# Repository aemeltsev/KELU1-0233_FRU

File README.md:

# KELU1-0233_FRU

![PCB image][KELU1-0233_FRU
]

[KELU1-0233_FRU]:https://github.com/aemeltsev/KELU1-0233_FRU/blob/master/hw/KELU1-0233_PCB.png

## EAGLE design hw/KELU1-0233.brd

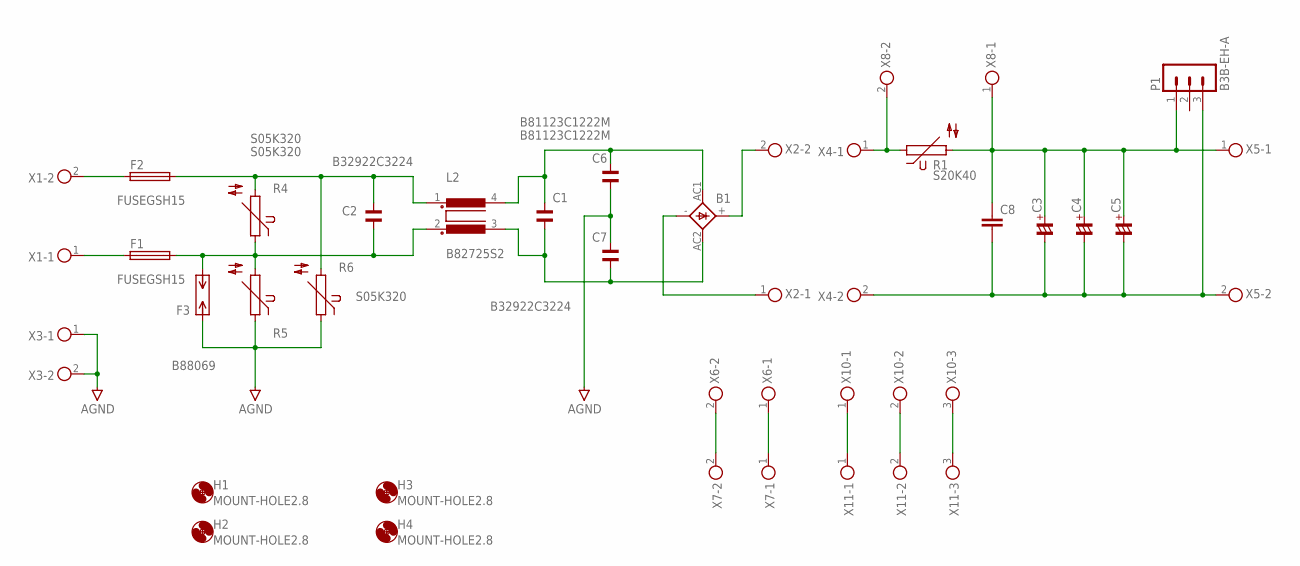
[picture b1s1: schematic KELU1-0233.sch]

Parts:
B1: FBM
C1, C2: B32922C3224; C150-054X183
C3, C4, C5: CPOL-EUE7.5-18; E7,5-18
C6, C7: B81123C1222M; C150-054X183
C8: C-EU102-043X133; C102-043X133
F1, F2: FUSEGSH15; GSH15
F3: B88069; N81
H1, H2, H3, H4: MOUNT-HOLE2.8; 2,8
L2: B82725S2; PLC
P1: B3B-EH-A
R1: S20K40
R4, R5, R6: S05K320; S05K300
X1, X2, X3, X4, X5, X6, X7, X8: DG129-7.5-02P; DG129-7.5-02P-14-00A
X10, X11: DG129-7.5-03P; DG129-7.5-03P-14-00A

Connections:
AGND: C6.2, C7.1, F3.P$1 (A), R5.1, R6.1, X3.1, X3.2
unnamed: C2.1, F2.2, L2.1, R4.2, R6.2
unnamed: C2.2, F1.2, F3.P$2 (B), L2.2, R4.1, R5.2
unnamed: F1.1, X1.1
unnamed: B1.AC1, C1.1, C6.1, L2.4
unnamed: B1.AC2, C1.2, C7.2, L2.3
unnamed: F2.1, X1.2
unnamed: B1.-, X2.1
unnamed: B1.+, X2.2
unnamed: C3.-, C4.-, C5.-, C8.2, P1.3, X4.2, X5.2
unnamed: C3.+, C4.+, C5.+, C8.1, P1.1, R1.2, X5.1, X8.1
unnamed: R1.1, X4.1, X8.2
unnamed: X6.2, X7.2
unnamed: X6.1, X7.1
unnamed: X10.1, X11.1
unnamed: X10.2, X11.2
unnamed: X10.3, X11.3

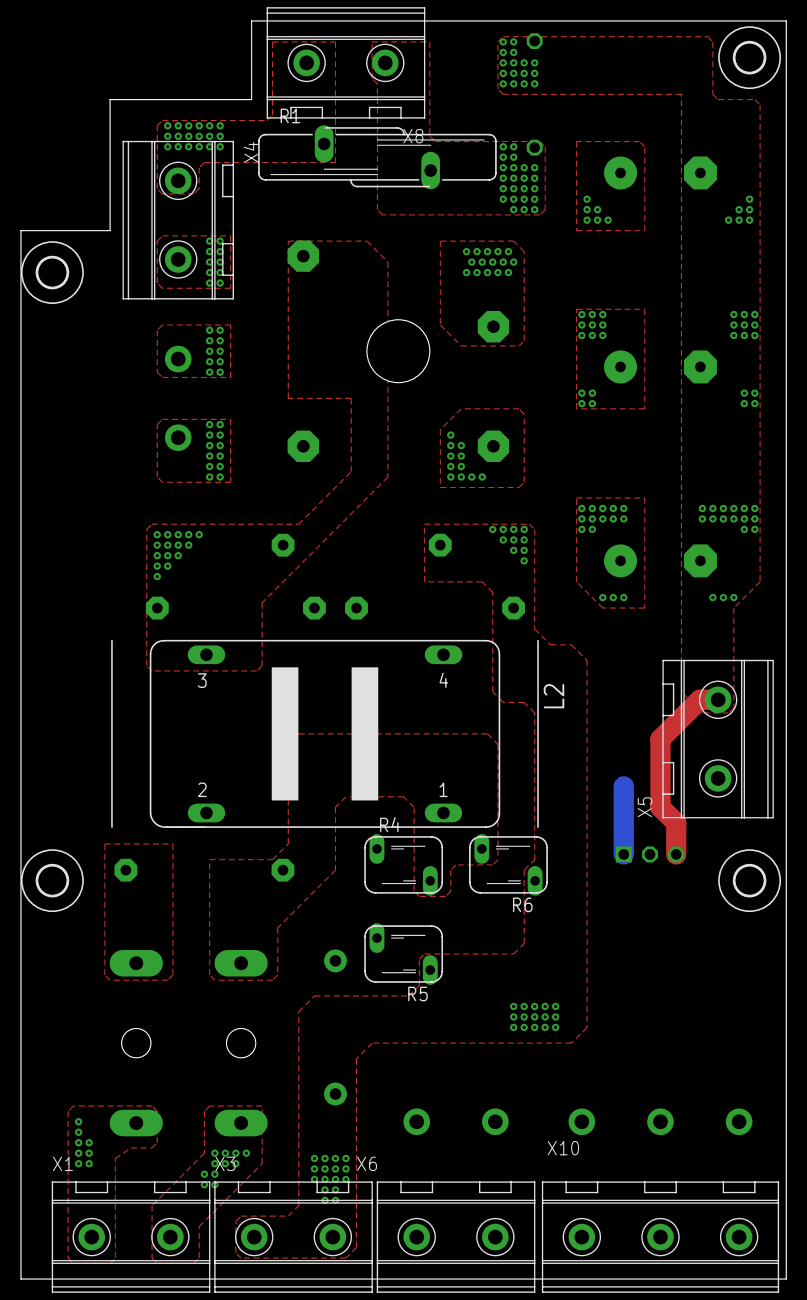
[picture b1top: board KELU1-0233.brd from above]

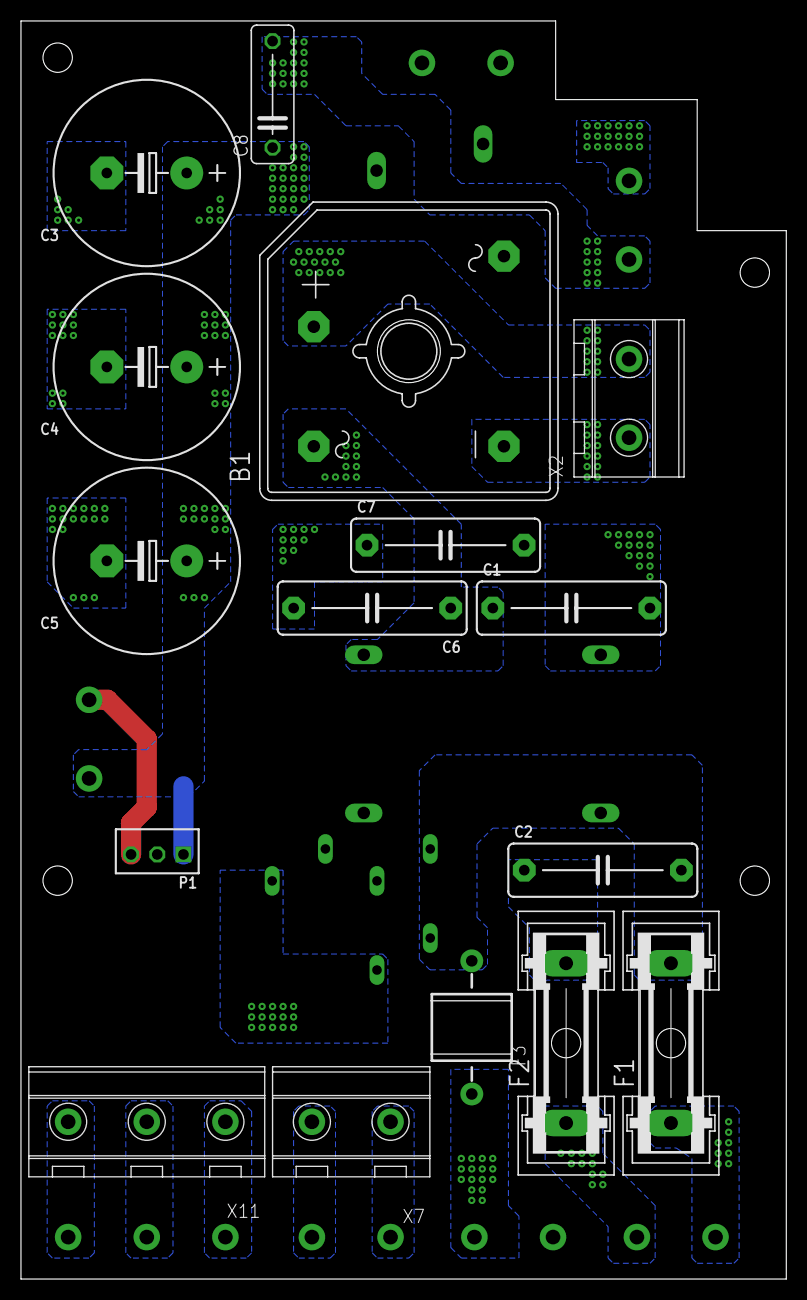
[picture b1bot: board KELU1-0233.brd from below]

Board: 2 copper layers, 73.0 x 120.0 mm, 32 parts (16 on the bottom side), 17 nets.

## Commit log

2019-01-29 Add Files
    Add project files
2019-01-29 Add file
    Add image pcb
2019-01-29 Update README.md
    Add image pcb
2019-01-29 Update KELU1-0233_PCB.png
    Editing pcb image
2019-01-29 Create KELU1-0233_PCB.png
    Add pcb image

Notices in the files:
parts and their libraries:
con-jst-eh: Copyright (C) 2016, Bob Starr
